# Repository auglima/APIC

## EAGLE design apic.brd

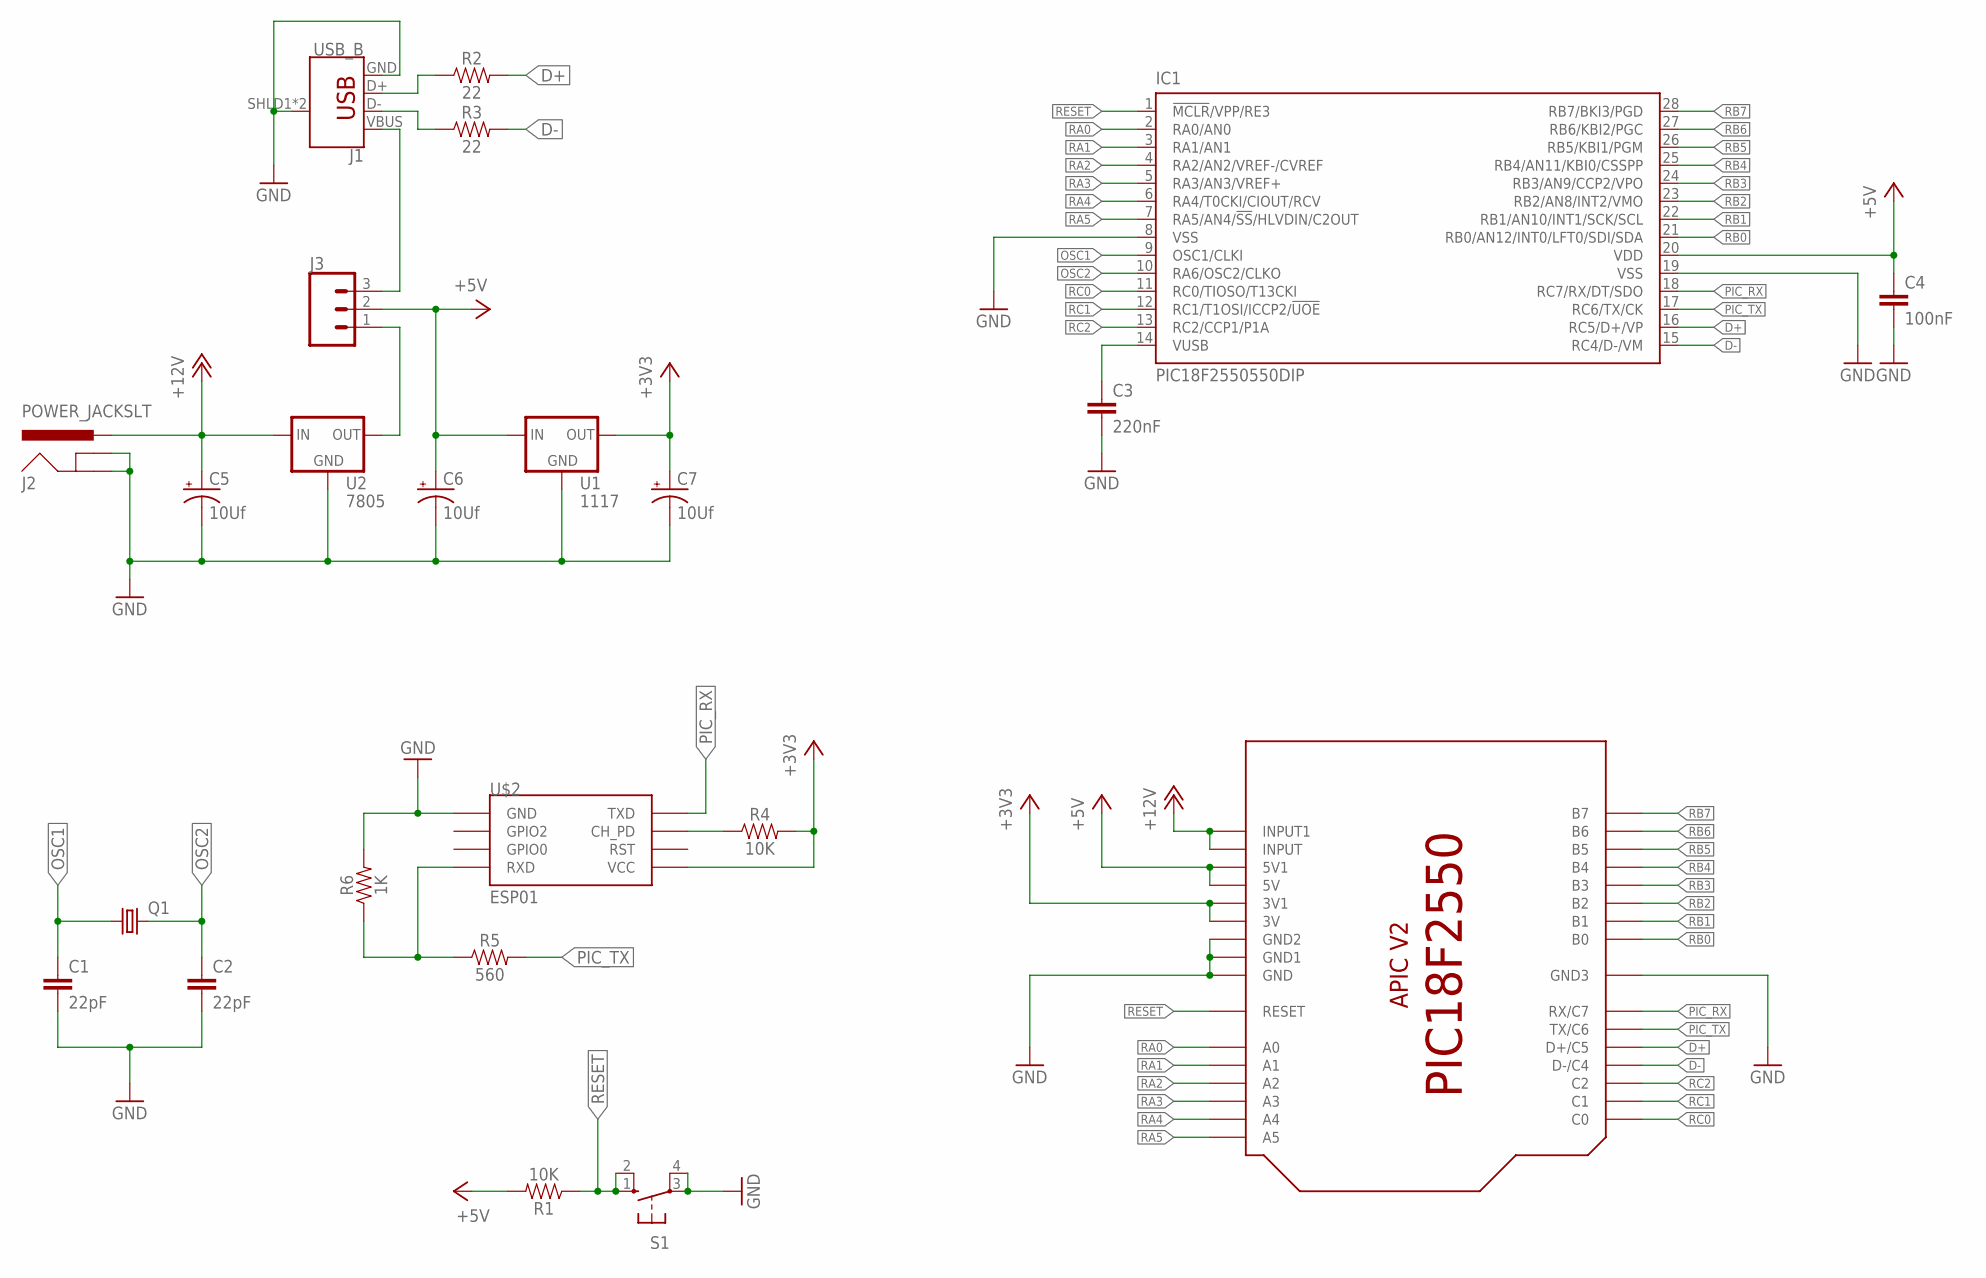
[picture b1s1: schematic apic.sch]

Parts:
C1, C2: 22pF; CAP-PTH-SMALL-KIT
C3: 220nF; CAP-PTH-5MM
C4: 100nF; CAP-PTH-SMALL-KIT
C5, C6, C7: 10Uf; CPOL-RADIAL-2.5MM-5MM
IC1: PIC18F2550550DIP; SOCKET_DIL28
J1: USB_B; USB-B
J2: POWER_JACKSLT; POWER_JACK
J3: CONN_03LONGPADS; 1X03_LONGPADS
Q1: CRYSTAL
R1, R4: 10K; AXIAL-0.3
R2, R3: 22; AXIAL-0.3
R5: 560; AXIAL-0.3
R6: 1K; AXIAL-0.3
S1: BUTTON
U1: 1117; TO-220-ALT
U2: 7805; TO-220-ALT
U$1: APIC-18F2550
U$2: ESP01

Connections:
+3V3: C7.+, R4.P$2 (2), U1.2 (OUT), U$1.3V, U$1.3V1, U$2.VCC
+5V: C4.1, C6.+, IC1.20 (VDD), J3.2, R1.P$2 (2), U1.3 (IN), U$1.5V, U$1.5V1
+12V: C5.+, J2.PWR, U2.1 (IN), U$1.INPUT, U$1.INPUT1
D+: IC1.16 (RC5/D+/VP), R2.P$2 (2), U$1.C5 (D+/C5)
D-: IC1.15 (RC4/D-/VM), R3.P$2 (2), U$1.C4 (D-/C4)
GND: C1.2, C2.2, C3.2, C4.2, C5.-, C6.-, C7.-, IC1.8 (VSS), IC1.19 (VSS), J1.GND, J1.SHLD1 (SHIELD), J1.SHLD2 (SHIELD), J2.GND@1 (GNDBREAK), J2.GND@2 (GND), R6.P$2 (2), S1.3, S1.4 (P1), U1.1 (GND), U2.2 (GND), U$1.GND, U$1.GND1, U$1.GND2, U$1.GND3, U$2.GND
unnamed: J1.D+, R2.P$1 (1)
unnamed: J1.D-, R3.P$1 (1)
unnamed: C3.1, IC1.14 (VUSB)
unnamed: J3.1, U2.3 (OUT)
unnamed: J1.VBUS, J3.3
unnamed: R4.P$1 (1), U$2.CH_PD
unnamed: R5.P$1 (1), R6.P$1 (1), U$2.RX (RXD)
OSC1: C1.1, IC1.9 (OSC1/CLKI), Q1.1
OSC2: C2.1, IC1.10 (RA6/OSC2/CLKO), Q1.2
PIC_RX: IC1.18 (RC7/RX/DT/SDO), U$1.C7 (RX/C7), U$2.TX (TXD)
PIC_TX: IC1.17 (RC6/TX/CK), R5.P$2 (2), U$1.C6 (TX/C6)
RA0: IC1.2 (RA0/AN0), U$1.A0
RA1: IC1.3 (RA1/AN1), U$1.A1
RA2: IC1.4 (RA2/AN2/VREF-/CVREF), U$1.A2
RA3: IC1.5 (RA3/AN3/VREF+), U$1.A3
RA4: IC1.6 (RA4/T0CKI/CIOUT/RCV), U$1.A4
RA5: IC1.7 (RA5/AN4/!SS!/HLVDIN/C2OUT), U$1.A5
RB0: IC1.21 (RB0/AN12/INT0/LFT0/SDI/SDA), U$1.B0
RB1: IC1.22 (RB1/AN10/INT1/SCK/SCL), U$1.B1
RB2: IC1.23 (RB2/AN8/INT2/VMO), U$1.B2
RB3: IC1.24 (RB3/AN9/CCP2/VPO), U$1.B3
RB4: IC1.25 (RB4/AN11/KBI0/CSSPP), U$1.B4
RB5: IC1.26 (RB5/KBI1/PGM), U$1.B5
RB6: IC1.27 (RB6/KBI2/PGC), U$1.B6
RB7: IC1.28 (RB7/BKI3/PGD), U$1.B7
RC0: IC1.11 (RC0/TIOSO/T13CKI), U$1.C0
RC1: IC1.12 (RC1/T1OSI/ICCP2/!UOE), U$1.C1
RC2: IC1.13 (RC2/CCP1/P1A), U$1.C2
RESET: IC1.1 (!MCLR!/VPP/RE3), R1.P$1 (1), S1.1 (S), S1.2 (S1), U$1.RESET

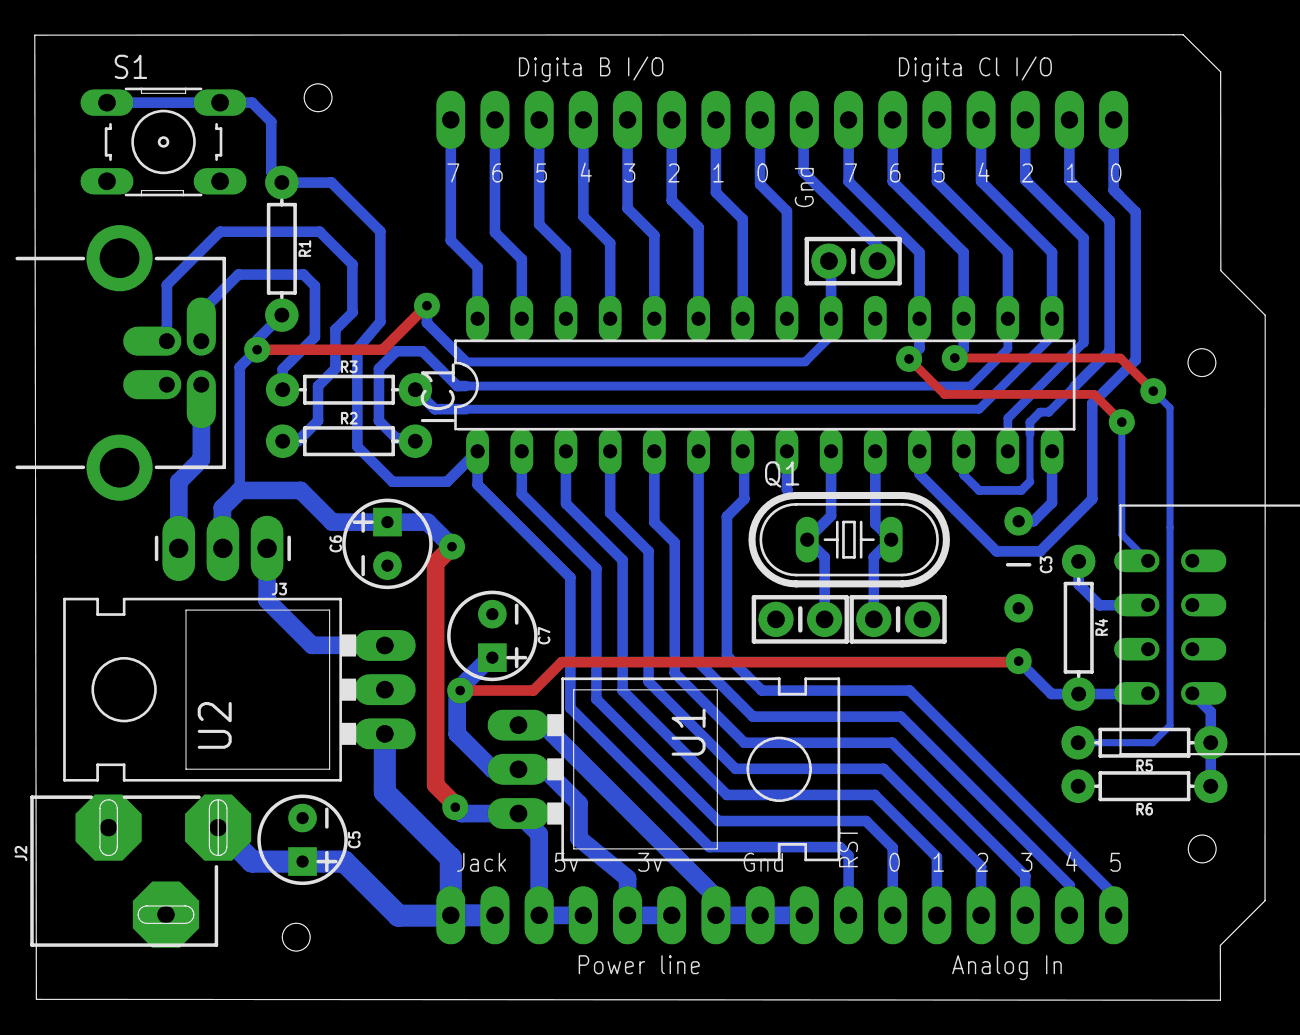
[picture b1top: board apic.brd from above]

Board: 2 copper layers, 70.7 x 55.5 mm, 23 parts (0 on the bottom side), 35 nets.

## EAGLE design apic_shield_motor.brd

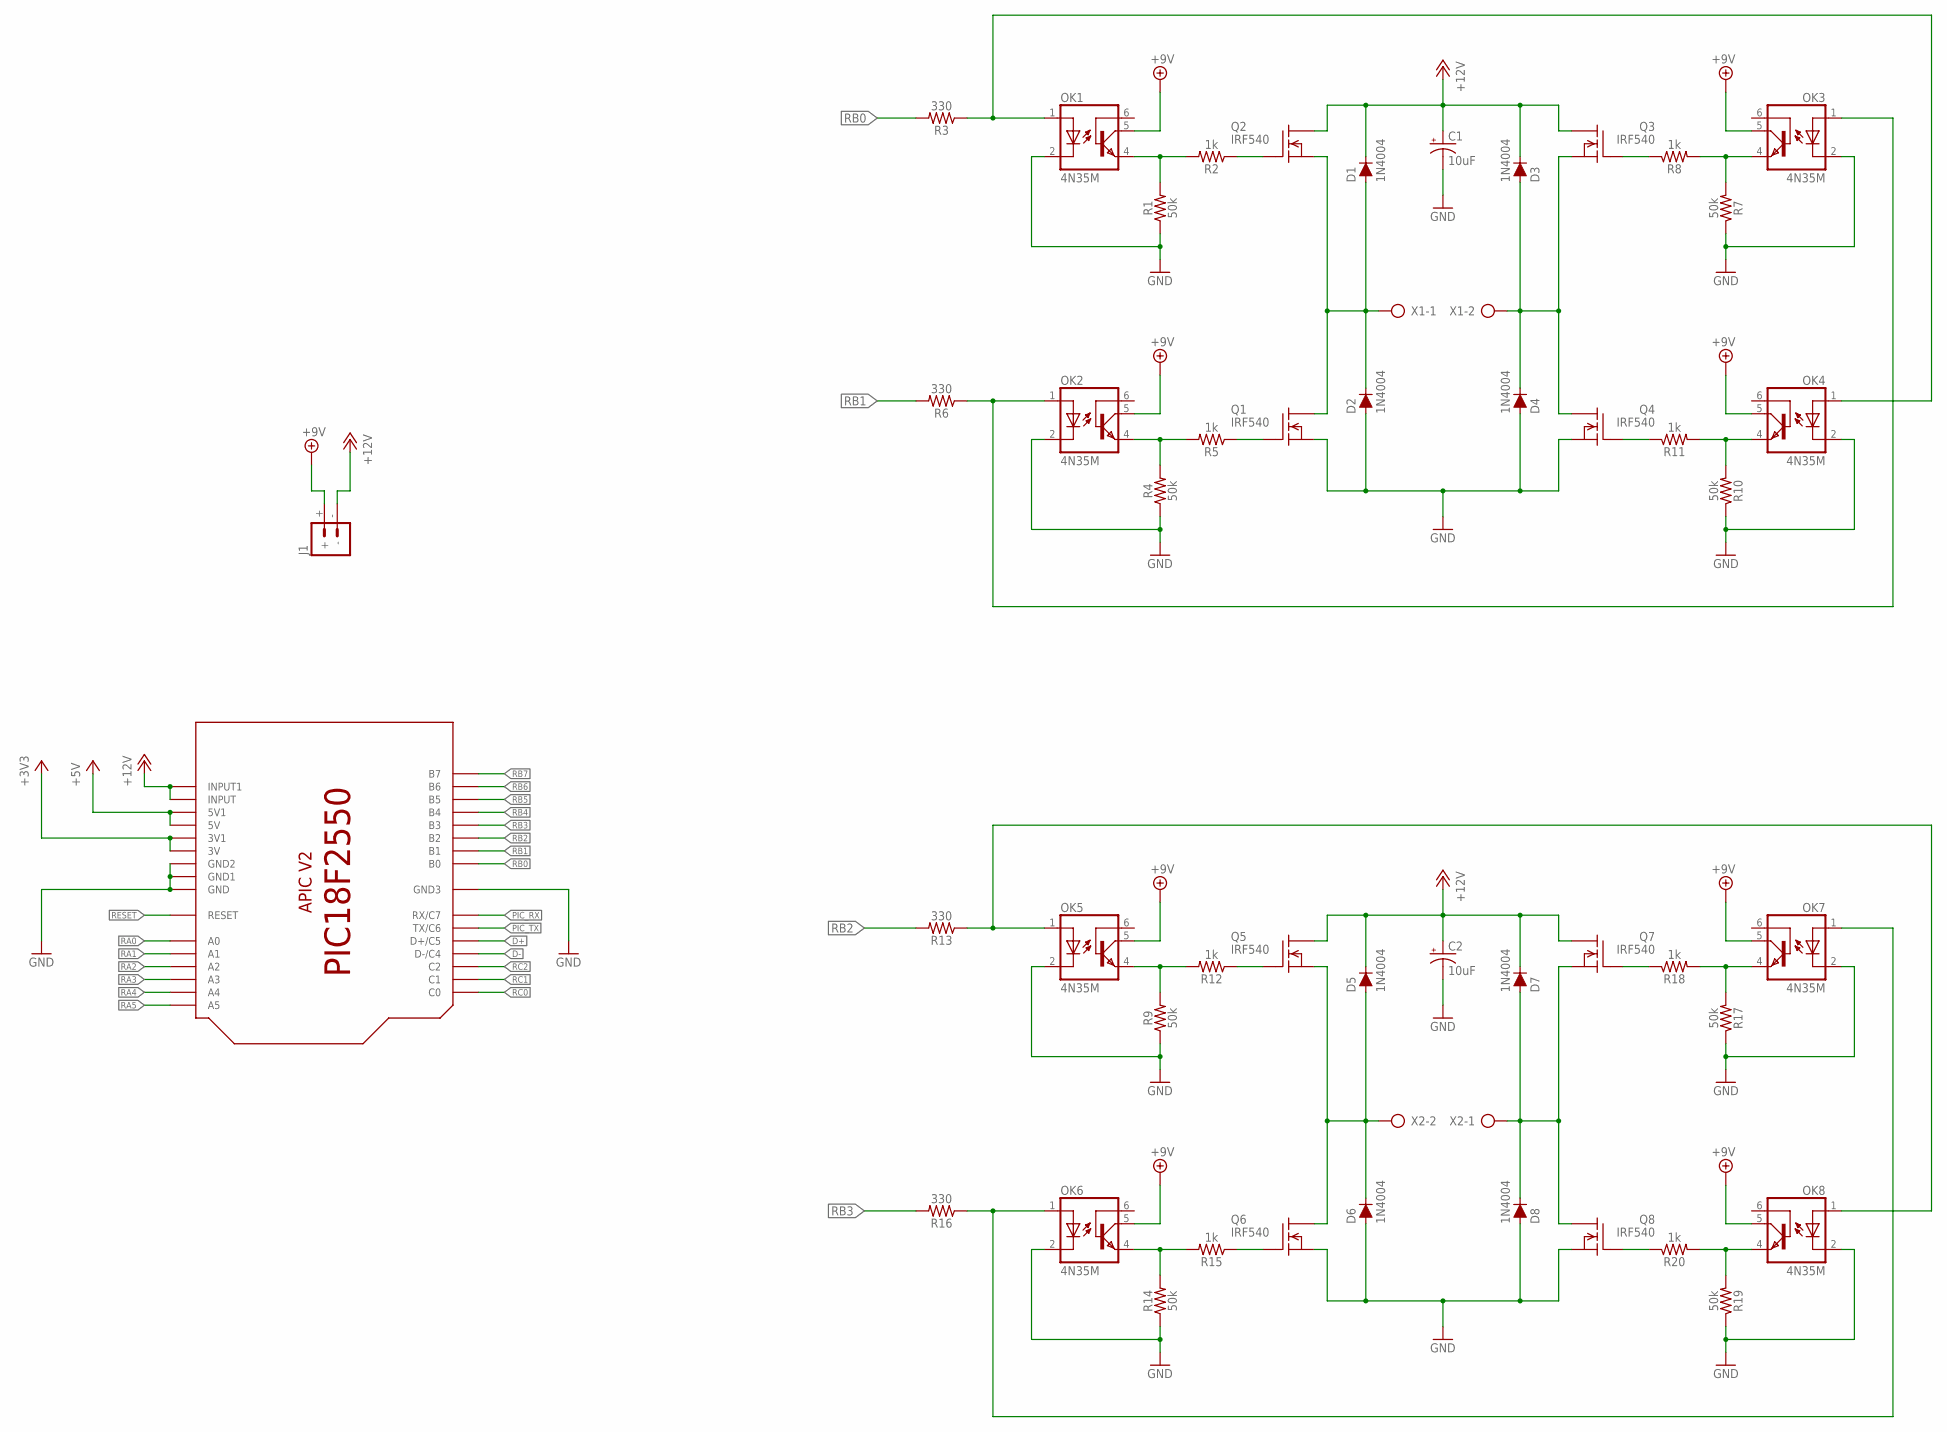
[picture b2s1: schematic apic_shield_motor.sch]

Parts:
C1, C2: 10uF; CPOL-RADIAL-2.5MM-5MM
D1, D2, D3, D4, D5, D6, D7, D8: 1N4004; DIODE-1N4001
J1: BATTERY_CONN_DEANS; DEANS
OK1, OK2, OK3, OK4, OK5, OK6, OK7, OK8: 4N35M; DIL06
Q1, Q2, Q3, Q4, Q5, Q6, Q7, Q8: IRF540; TO220V
R1, R4, R7, R9, R10, R14, R17, R19: 50k; AXIAL-0.3
R2, R5, R8, R11, R12, R15, R18, R20: 1k; AXIAL-0.3
R3, R6, R13, R16: 330; AXIAL-0.3
U$1: APIC-18F2550
X1, X2: AK500/2-H

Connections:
+3V3: U$1.3V, U$1.3V1
+5V: U$1.5V, U$1.5V1
+9V: J1.+, OK1.5 (COL), OK2.5 (COL), OK3.5 (COL), OK4.5 (COL), OK5.5 (COL), OK6.5 (COL), OK7.5 (COL), OK8.5 (COL)
+12V: C1.1 (+), C2.1 (+), D1.C, D3.C, D5.C, D7.C, J1.-, Q2.2 (D), Q3.2 (D), Q5.2 (D), Q7.2 (D), U$1.INPUT, U$1.INPUT1
D+: U$1.C5 (D+/C5)
D-: U$1.C4 (D-/C4)
GND: C1.2 (-), C2.2 (-), D2.A, D4.A, D6.A, D8.A, OK1.2 (C), OK2.2 (C), OK3.2 (C), OK4.2 (C), OK5.2 (C), OK6.2 (C), OK7.2 (C), OK8.2 (C), Q1.3 (S), Q4.3 (S), Q6.3 (S), Q8.3 (S), R1.P$1 (1), R4.P$1 (1), R7.P$1 (1), R9.P$1 (1), R10.P$1 (1), R14.P$1 (1), R17.P$1 (1), R19.P$1 (1), U$1.GND, U$1.GND1, U$1.GND2, U$1.GND3
unnamed: OK1.4 (EMI), R1.P$2 (2), R2.P$2 (2)
unnamed: Q2.1 (G), R2.P$1 (1)
unnamed: OK2.4 (EMI), R4.P$2 (2), R5.P$2 (2)
unnamed: OK1.1 (A), OK4.1 (A), R3.P$1 (1)
unnamed: Q1.1 (G), R5.P$1 (1)
unnamed: OK5.4 (EMI), R9.P$2 (2), R12.P$2 (2)
unnamed: D1.A, D2.C, Q1.2 (D), Q2.3 (S), X1.1
unnamed: OK3.4 (EMI), R7.P$2 (2), R8.P$2 (2)
unnamed: OK2.1 (A), OK3.1 (A), R6.P$1 (1)
unnamed: Q3.1 (G), R8.P$1 (1)
unnamed: Q5.1 (G), R12.P$1 (1)
unnamed: OK6.4 (EMI), R14.P$2 (2), R15.P$2 (2)
unnamed: OK4.4 (EMI), R10.P$2 (2), R11.P$2 (2)
unnamed: Q4.1 (G), R11.P$1 (1)
unnamed: D3.A, D4.C, Q3.3 (S), Q4.2 (D), X1.2
unnamed: Q6.1 (G), R15.P$1 (1)
unnamed: OK6.1 (A), OK7.1 (A), R16.P$1 (1)
unnamed: OK7.4 (EMI), R17.P$2 (2), R18.P$2 (2)
unnamed: Q7.1 (G), R18.P$1 (1)
unnamed: OK8.4 (EMI), R19.P$2 (2), R20.P$2 (2)
unnamed: Q8.1 (G), R20.P$1 (1)
unnamed: D5.A, D6.C, Q5.3 (S), Q6.2 (D), X2.2
unnamed: D7.A, D8.C, Q7.3 (S), Q8.2 (D), X2.1
unnamed: OK5.1 (A), OK8.1 (A), R13.P$1 (1)
PIC_RX: U$1.C7 (RX/C7)
PIC_TX: U$1.C6 (TX/C6)
RA0: U$1.A0
RA1: U$1.A1
RA2: U$1.A2
RA3: U$1.A3
RA4: U$1.A4
RA5: U$1.A5
RB0: R3.P$2 (2), U$1.B0
RB1: R6.P$2 (2), U$1.B1
RB2: R13.P$2 (2), U$1.B2
RB3: R16.P$2 (2), U$1.B3
RB4: U$1.B4
RB5: U$1.B5
RB6: U$1.B6
RB7: U$1.B7
RC0: U$1.C0
RC1: U$1.C1
RC2: U$1.C2
RESET: U$1.RESET

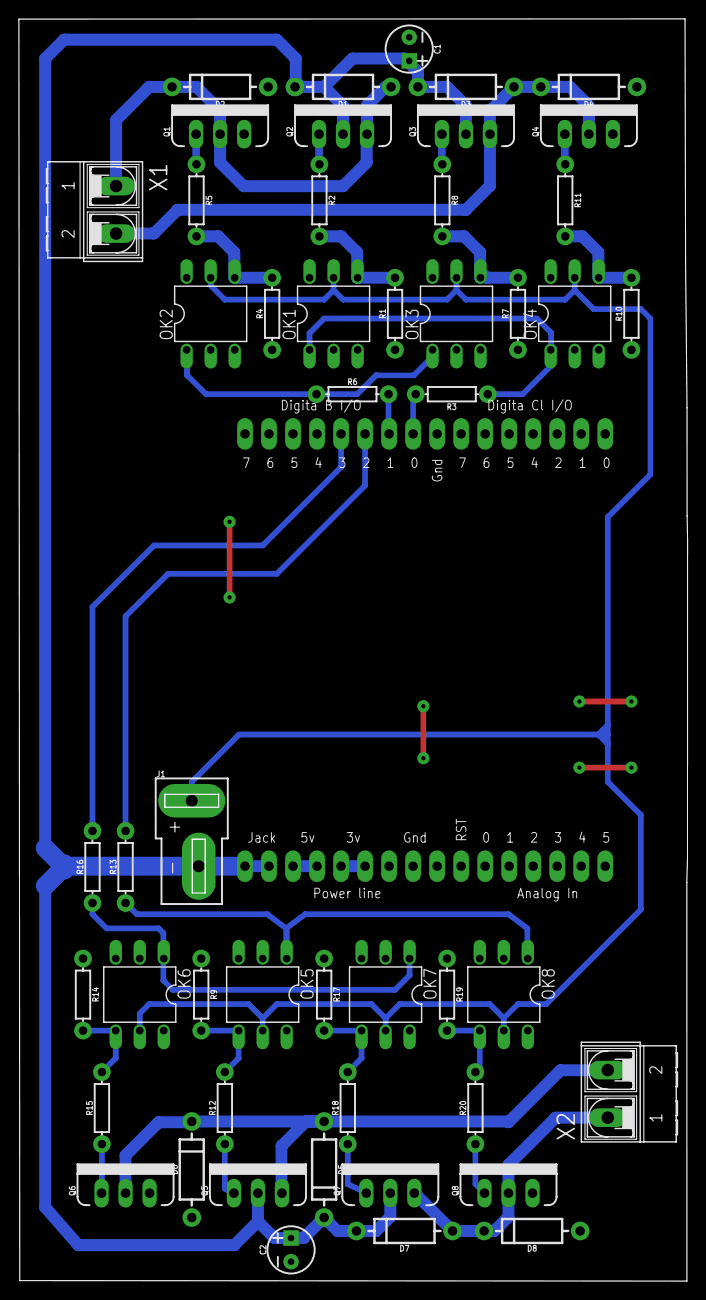
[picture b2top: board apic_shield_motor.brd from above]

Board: 2 copper layers, 70.7 x 133.5 mm, 50 parts (0 on the bottom side), 33 nets.

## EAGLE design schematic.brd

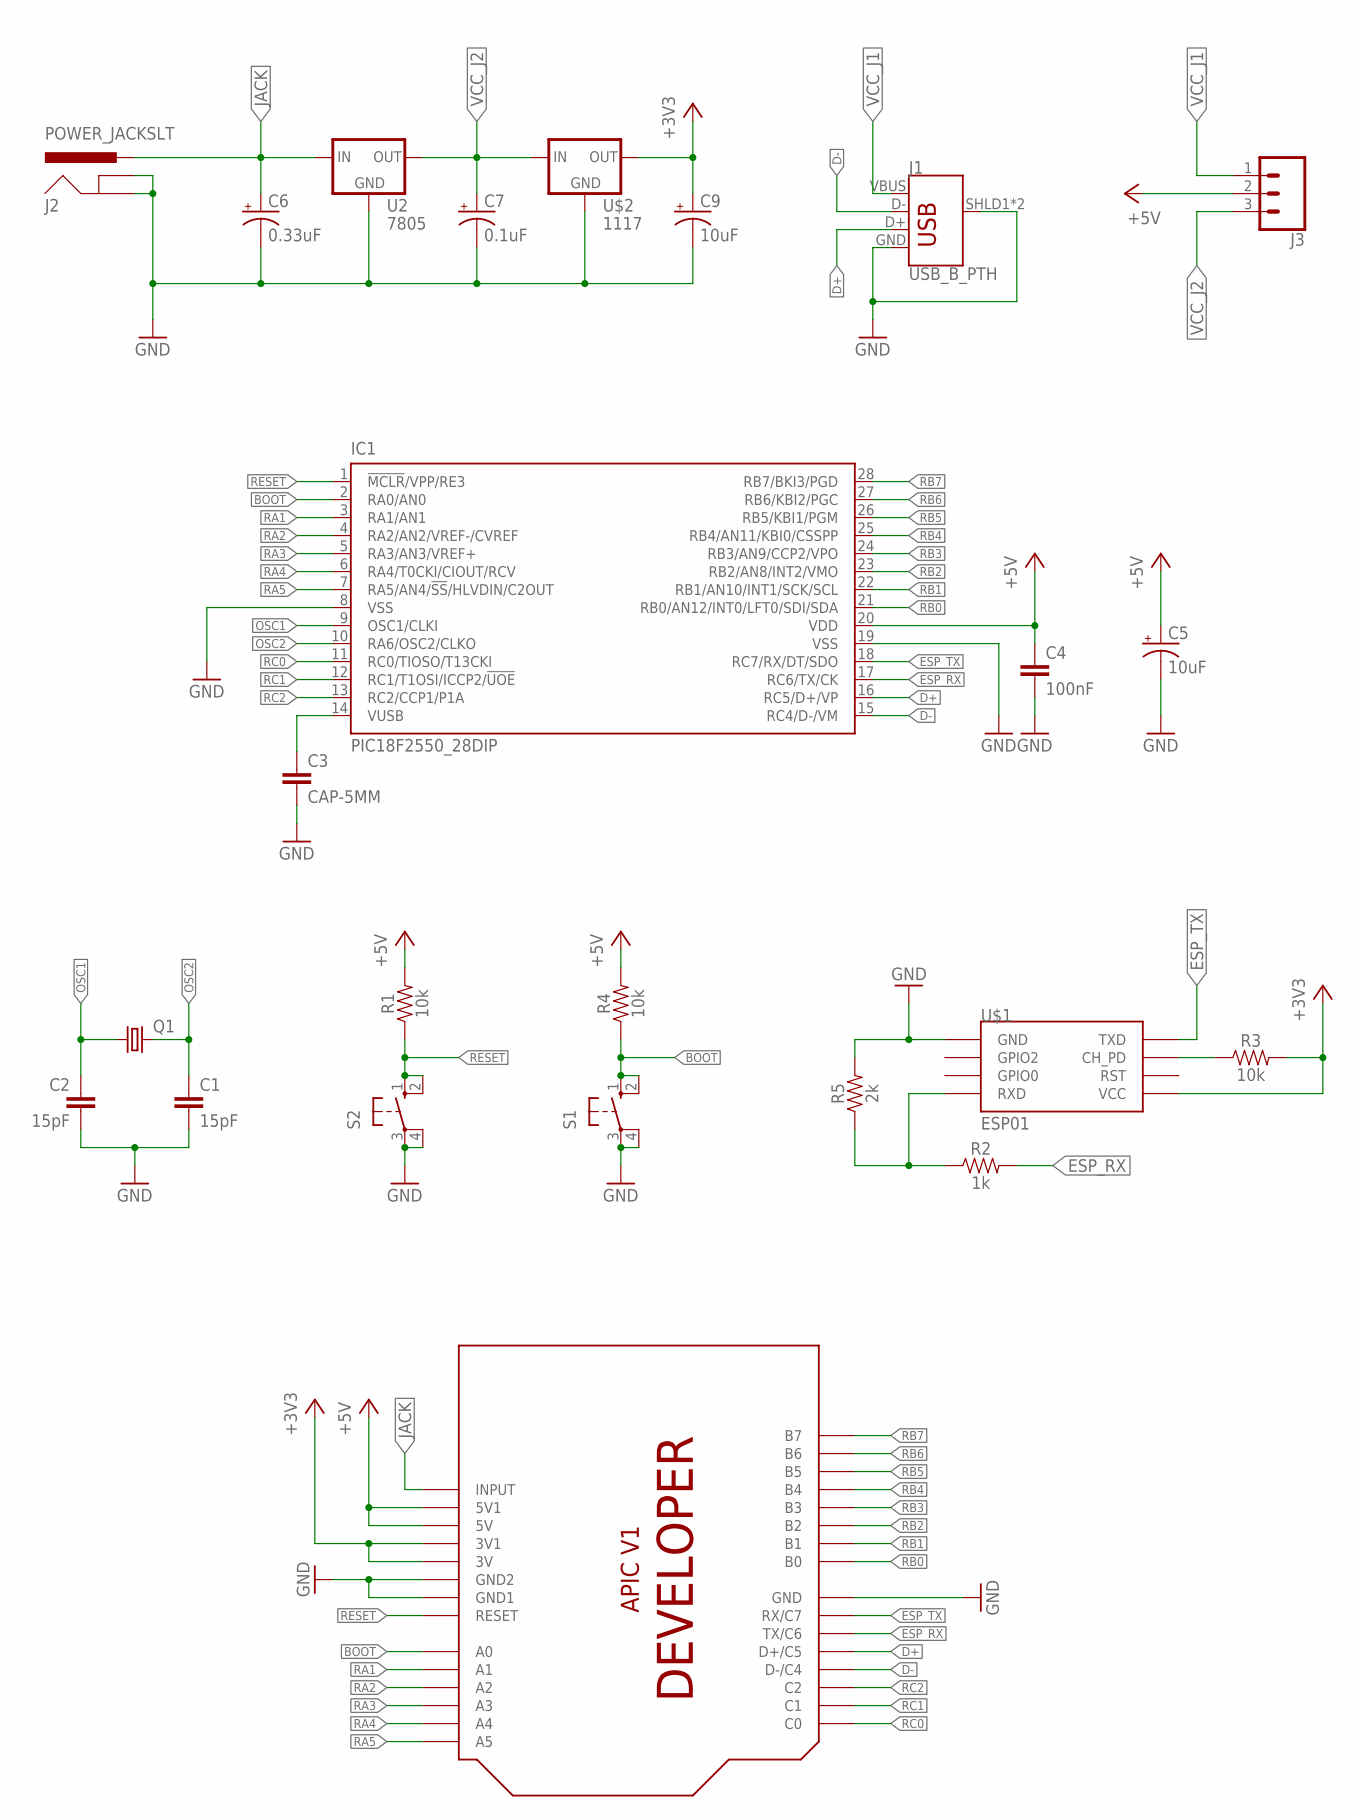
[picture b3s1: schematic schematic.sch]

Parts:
C1, C2: 15pF; CAP-PTH-SMALL-KIT
C3: CAP-5MM; CAP-PTH-5MM
C4: 100nF; CAP-PTH-SMALL-KIT
C5, C9: 10uF; CPOL-RADIAL-2.5MM-5MM
C6: 0.33uF; CPOL-RADIAL-2.5MM-5MM
C7: 0.1uF; CPOL-RADIAL-2.5MM-5MM
IC1: PIC18F2550_28DIP; DIL28-3
J1: USB_B_PTH; USB-B-PTH
J2: POWER_JACKSLT; POWER_JACK_SLOT
J3: CONN_03LOCK_LONGPADS; 1X03_LOCK_LONGPADS
Q1: CRYSTAL; HC49U70
R1, R3, R4: 10k; AXIAL-0.3
R2: 1k; AXIAL-0.3
R5: 2k; AXIAL-0.3
S1, S2: 10-XX; B3F-10XX
U1: APIC-BPLACE; APIC
U2: 7805; 78XXL
U$1: ESP01
U$2: 1117; 78XXL

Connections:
+3V3: C9.1 (+), R3.P$2 (2), U1.3V, U1.3V1, U$1.VCC, U$2.GND (OUT)
+5V: C4.1, C5.1 (+), IC1.20 (VDD), J3.2, R1.P$2 (2), R4.P$2 (2), U1.5V, U1.5V1
BOOT: IC1.2 (RA0/AN0), R4.P$1 (1), S1.1 (S), S1.2 (S1), U1.A0
D+: IC1.16 (RC5/D+/VP), J1.D+, U1.C5 (D+/C5)
D-: IC1.15 (RC4/D-/VM), J1.D-, U1.C4 (D-/C4)
ESP_RX: IC1.17 (RC6/TX/CK), R2.P$2 (2), U1.C6 (TX/C6)
ESP_TX: IC1.18 (RC7/RX/DT/SDO), U1.C7 (RX/C7), U$1.TX (TXD)
GND: C1.2, C2.2, C3.2, C4.2, C5.2 (-), C6.2 (-), C7.2 (-), C9.2 (-), IC1.8 (VSS), IC1.19 (VSS), J1.GND, J1.SHLD1 (SHIELD), J1.SHLD2 (SHIELD), J2.GND@1 (GNDBREAK), J2.GND@2 (GND), R5.P$2 (2), S1.3, S1.4 (P1), S2.3, S2.4 (P1), U1.GND, U1.GND1, U1.GND2, U2.GND, U$1.GND, U$2.IN (GND)
JACK: C6.1 (+), J2.PWR, U1.INPUT, U2.IN
unnamed: R3.P$1 (1), U$1.CH_PD
unnamed: R2.P$1 (1), R5.P$1 (1), U$1.RX (RXD)
unnamed: C3.1, IC1.14 (VUSB)
OSC1: C2.1, IC1.9 (OSC1/CLKI), Q1.1
OSC2: C1.1, IC1.10 (RA6/OSC2/CLKO), Q1.2
RA1: IC1.3 (RA1/AN1), U1.A1
RA2: IC1.4 (RA2/AN2/VREF-/CVREF), U1.A2
RA3: IC1.5 (RA3/AN3/VREF+), U1.A3
RA4: IC1.6 (RA4/T0CKI/CIOUT/RCV), U1.A4
RA5: IC1.7 (RA5/AN4/!SS!/HLVDIN/C2OUT), U1.A5
RB0: IC1.21 (RB0/AN12/INT0/LFT0/SDI/SDA), U1.B0
RB1: IC1.22 (RB1/AN10/INT1/SCK/SCL), U1.B1
RB2: IC1.23 (RB2/AN8/INT2/VMO), U1.B2
RB3: IC1.24 (RB3/AN9/CCP2/VPO), U1.B3
RB4: IC1.25 (RB4/AN11/KBI0/CSSPP), U1.B4
RB5: IC1.26 (RB5/KBI1/PGM), U1.B5
RB6: IC1.27 (RB6/KBI2/PGC), U1.B6
RB7: IC1.28 (RB7/BKI3/PGD), U1.B7
RC0: IC1.11 (RC0/TIOSO/T13CKI), U1.C0
RC1: IC1.12 (RC1/T1OSI/ICCP2/!UOE), U1.C1
RC2: IC1.13 (RC2/CCP1/P1A), U1.C2
RESET: IC1.1 (!MCLR!/VPP/RE3), R1.P$1 (1), S2.1 (S), S2.2 (S1), U1.RESET
VCC_J1: J1.VBUS, J3.1
VCC_J2: C7.1 (+), J3.3, U2.OUT, U$2.OUT (IN)

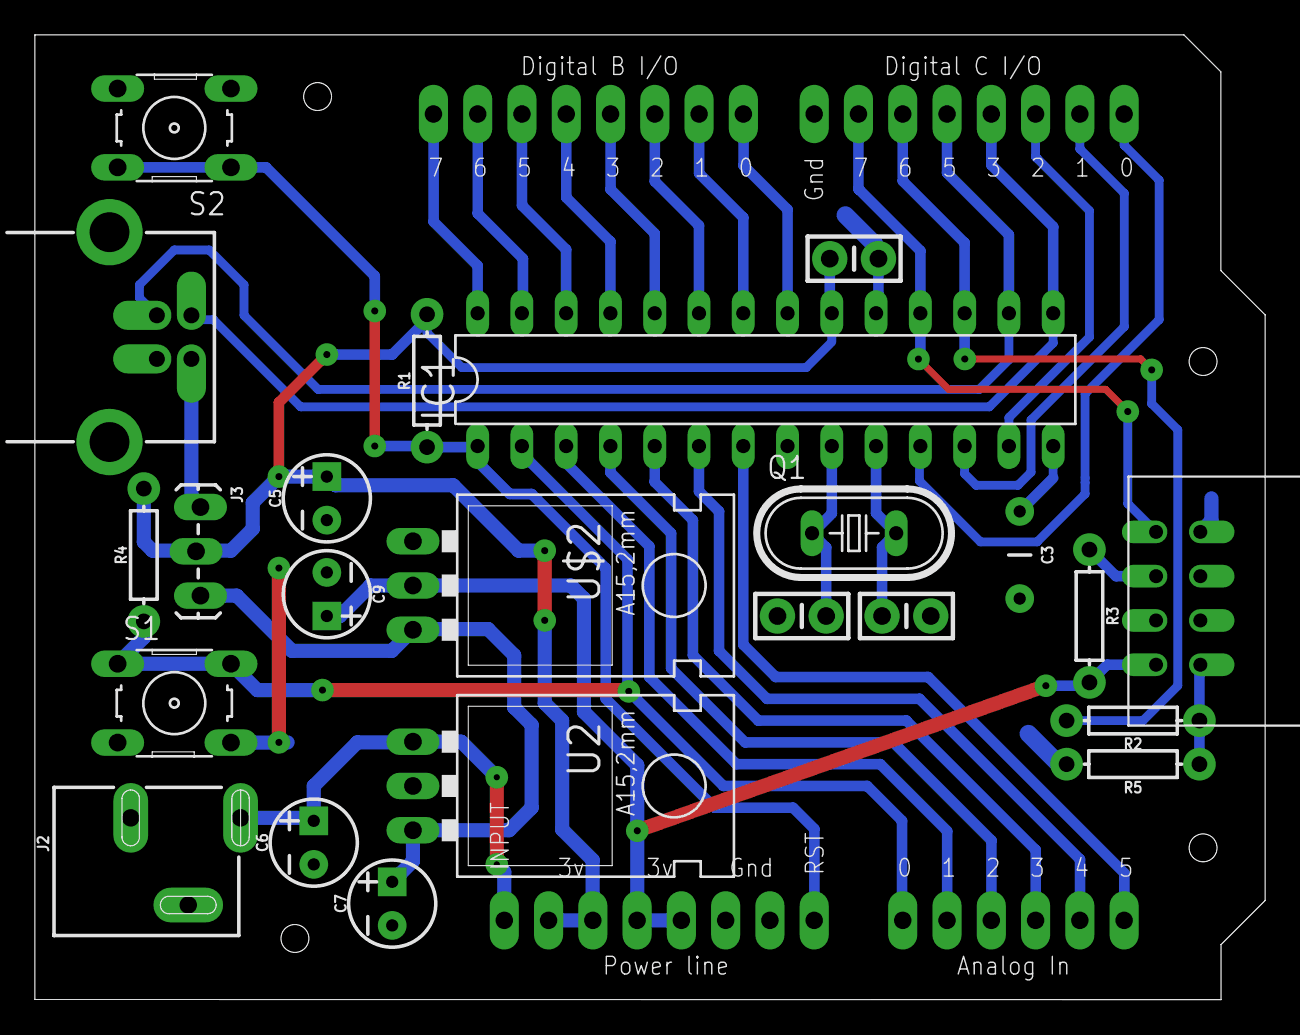
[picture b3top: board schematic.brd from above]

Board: 2 copper layers, 70.6 x 55.4 mm, 24 parts (0 on the bottom side), 33 nets.

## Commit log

2017-09-08 Create info
2017-10-02 update project

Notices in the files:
parts and their libraries:
SparkFun-Connectors: Licensing: Creative Commons ShareAlike 4.0 International - https://creativecommons.org/licenses/by-sa/4.0
